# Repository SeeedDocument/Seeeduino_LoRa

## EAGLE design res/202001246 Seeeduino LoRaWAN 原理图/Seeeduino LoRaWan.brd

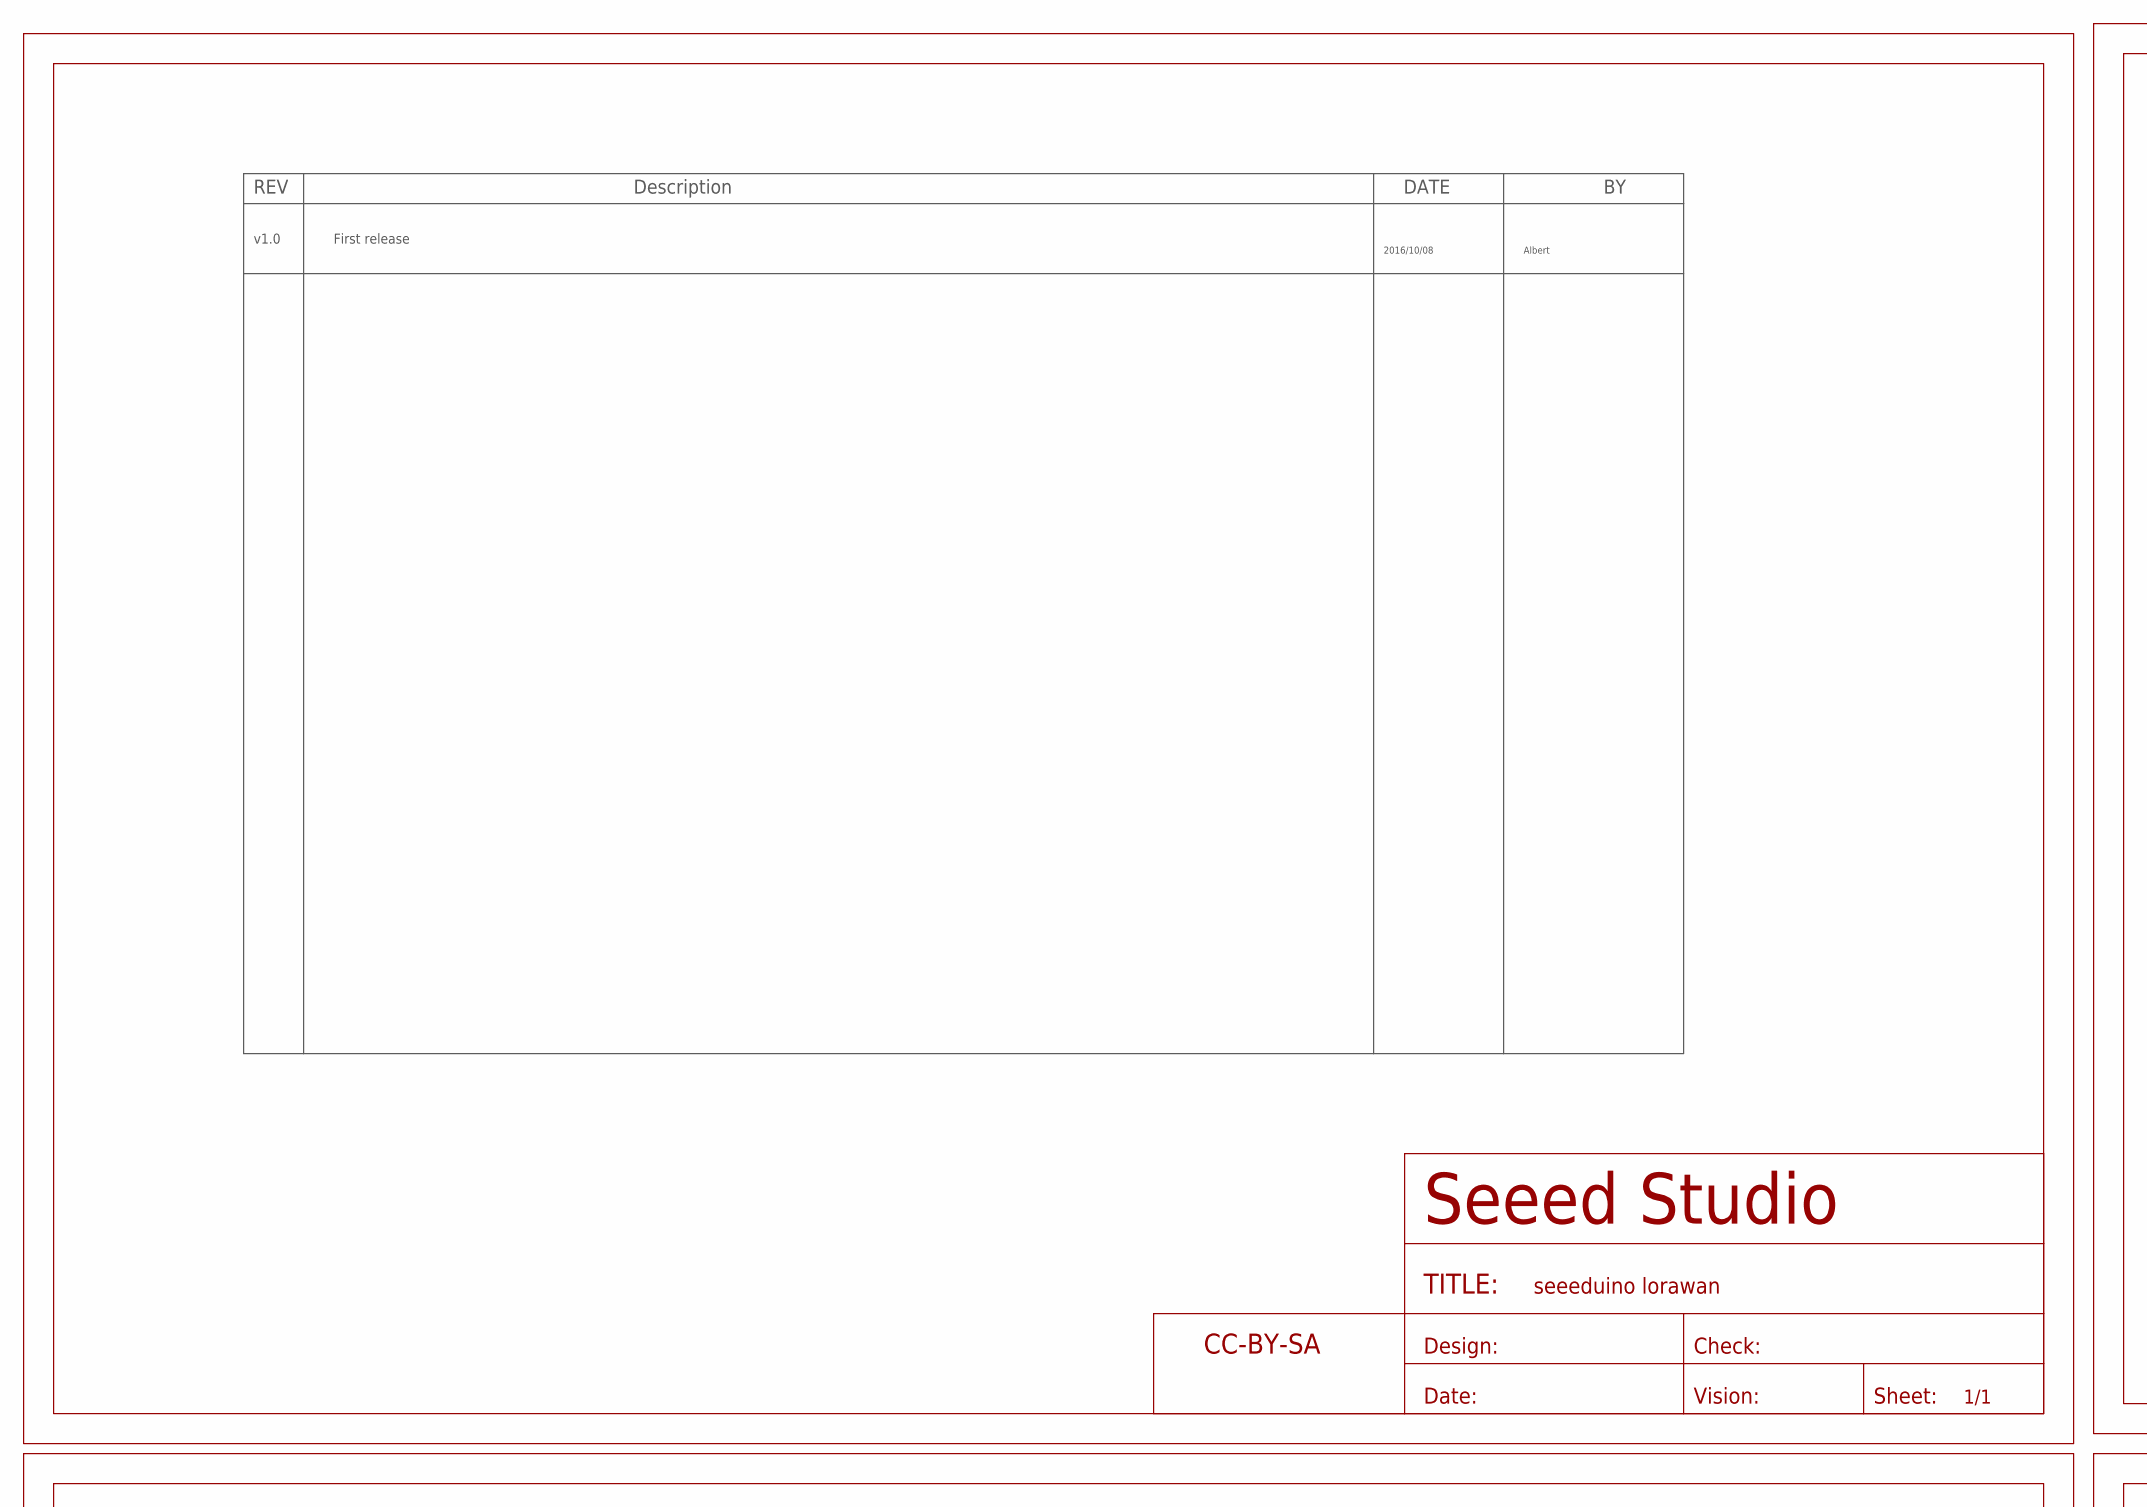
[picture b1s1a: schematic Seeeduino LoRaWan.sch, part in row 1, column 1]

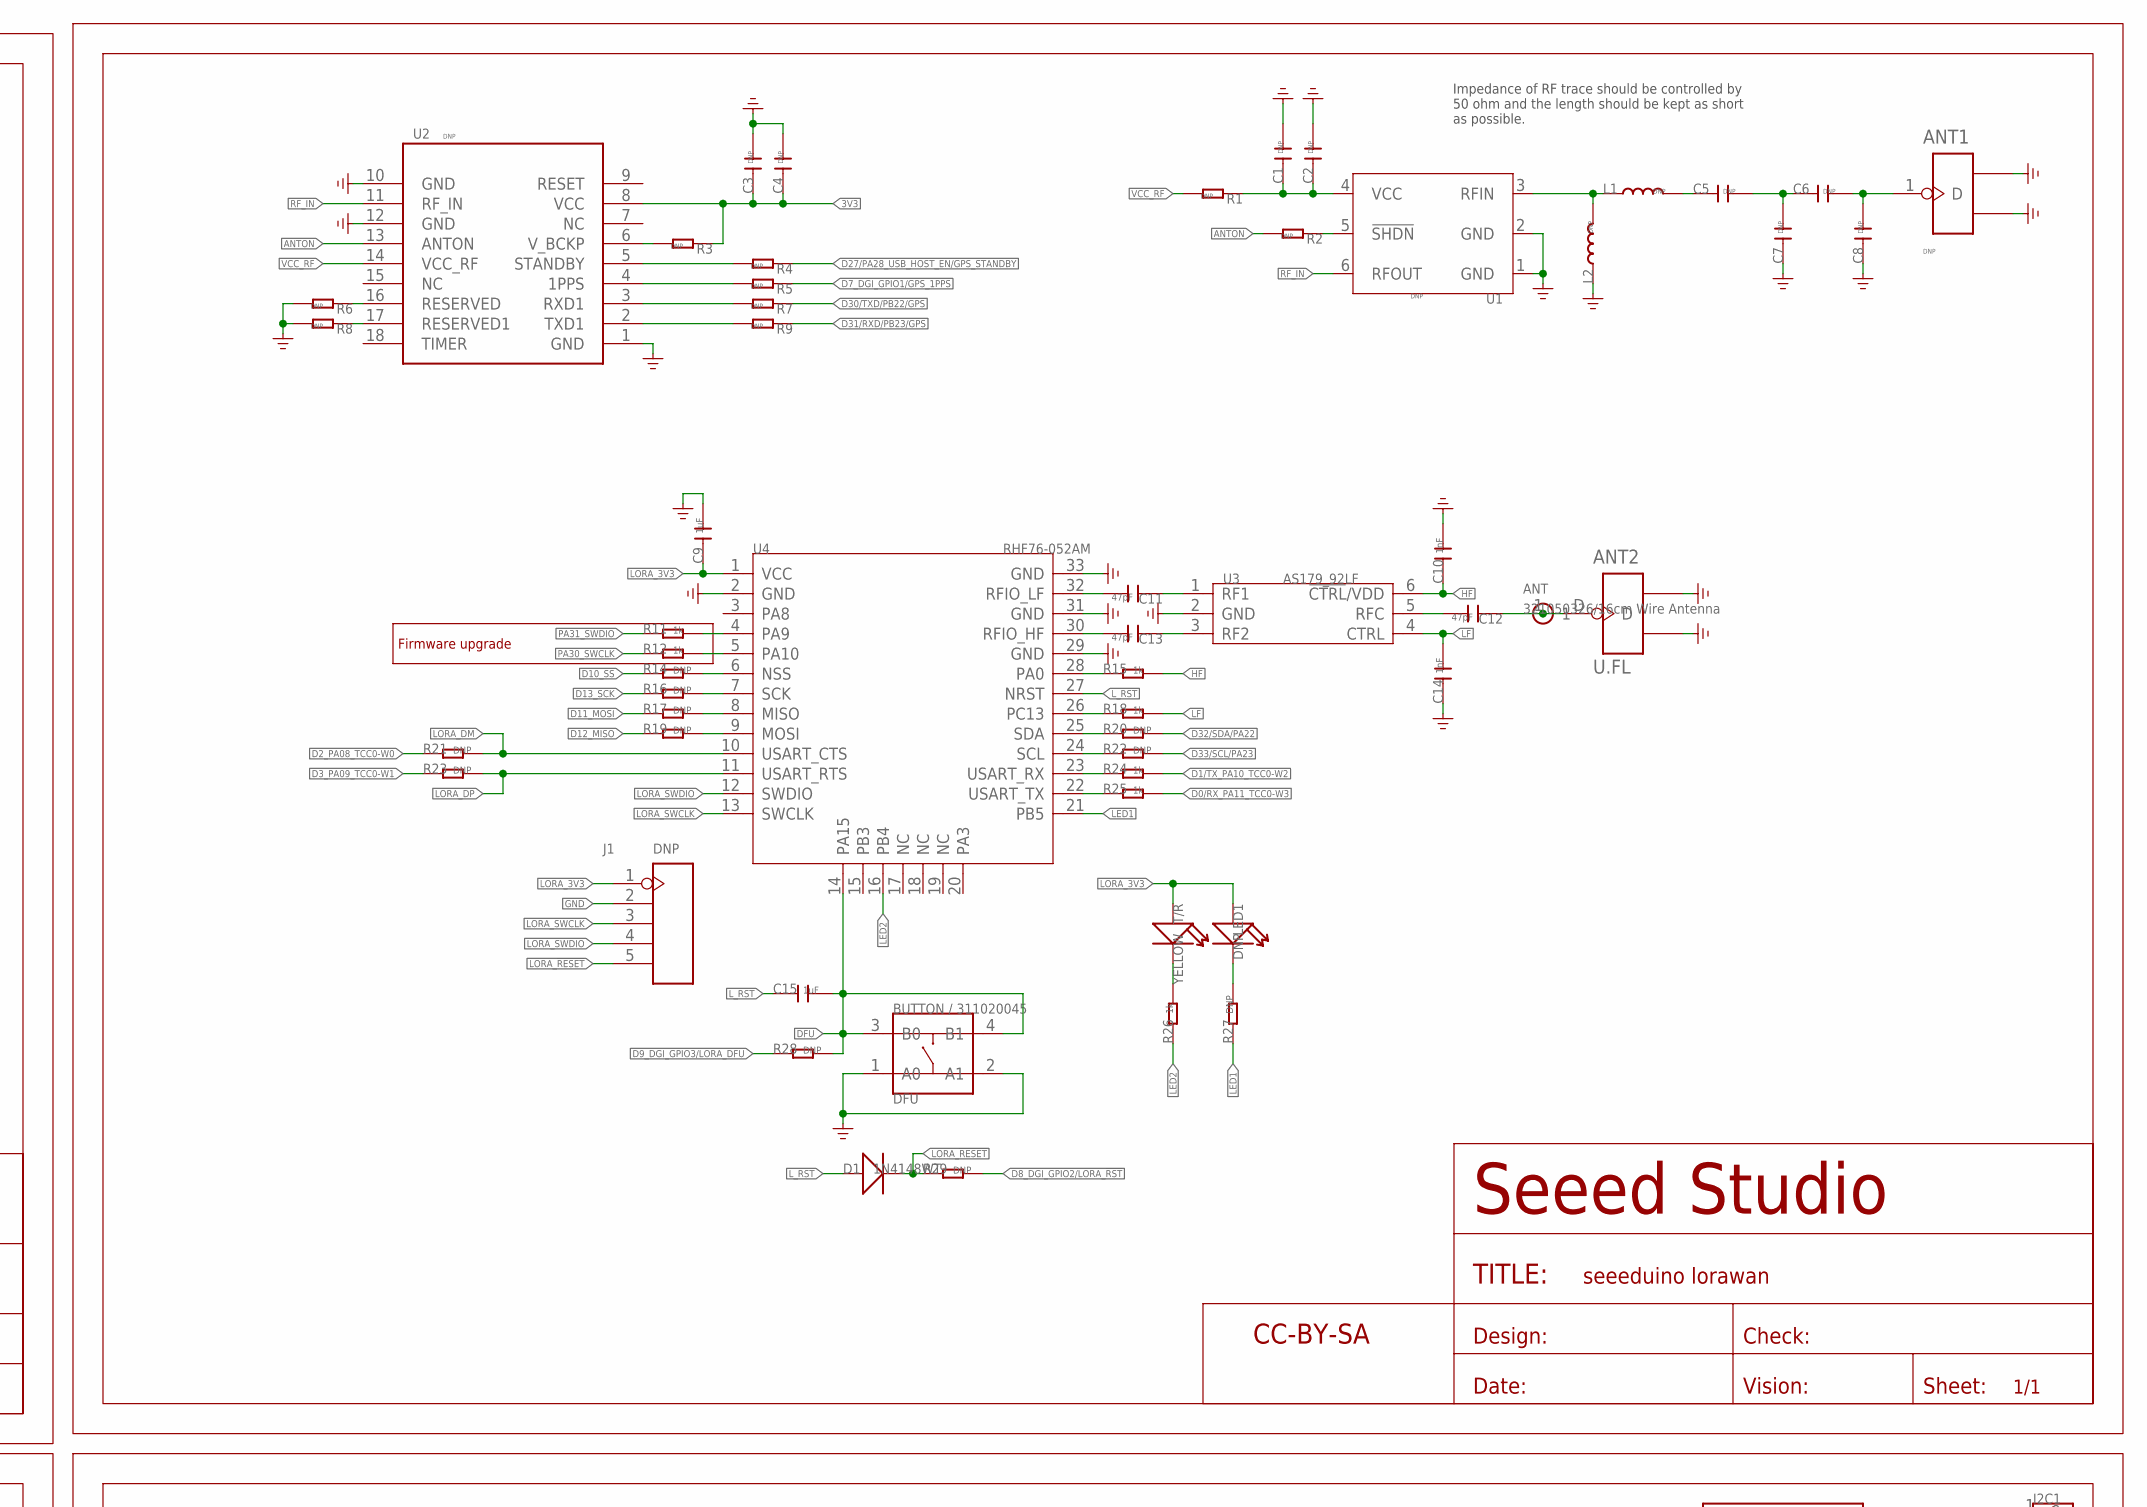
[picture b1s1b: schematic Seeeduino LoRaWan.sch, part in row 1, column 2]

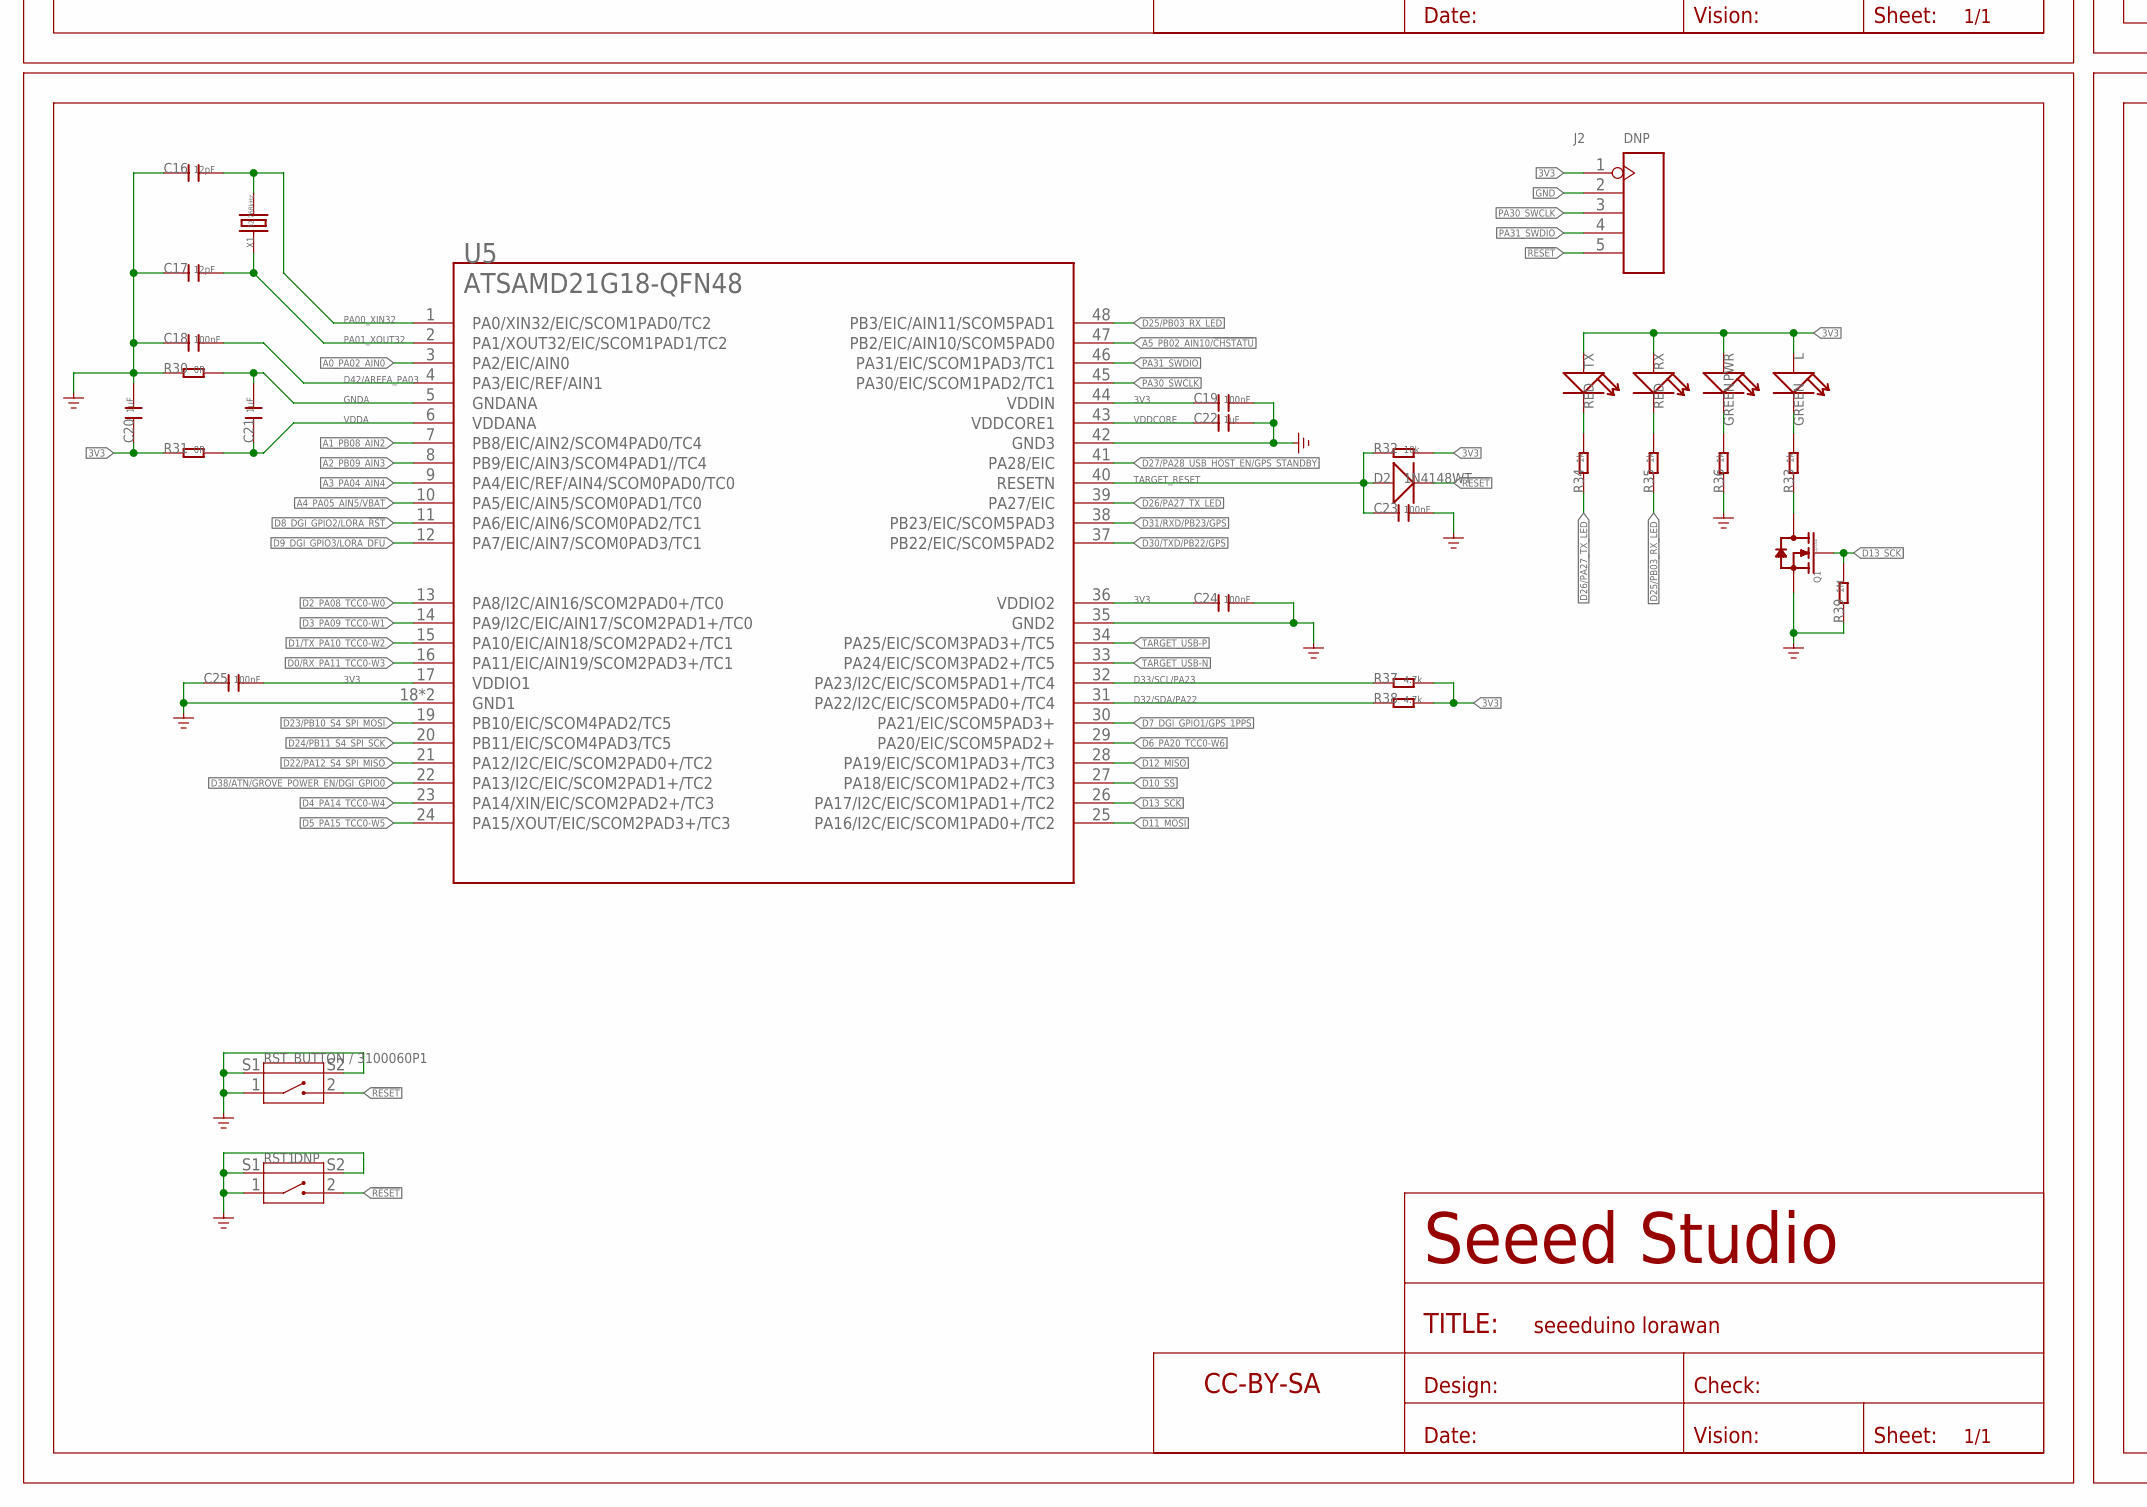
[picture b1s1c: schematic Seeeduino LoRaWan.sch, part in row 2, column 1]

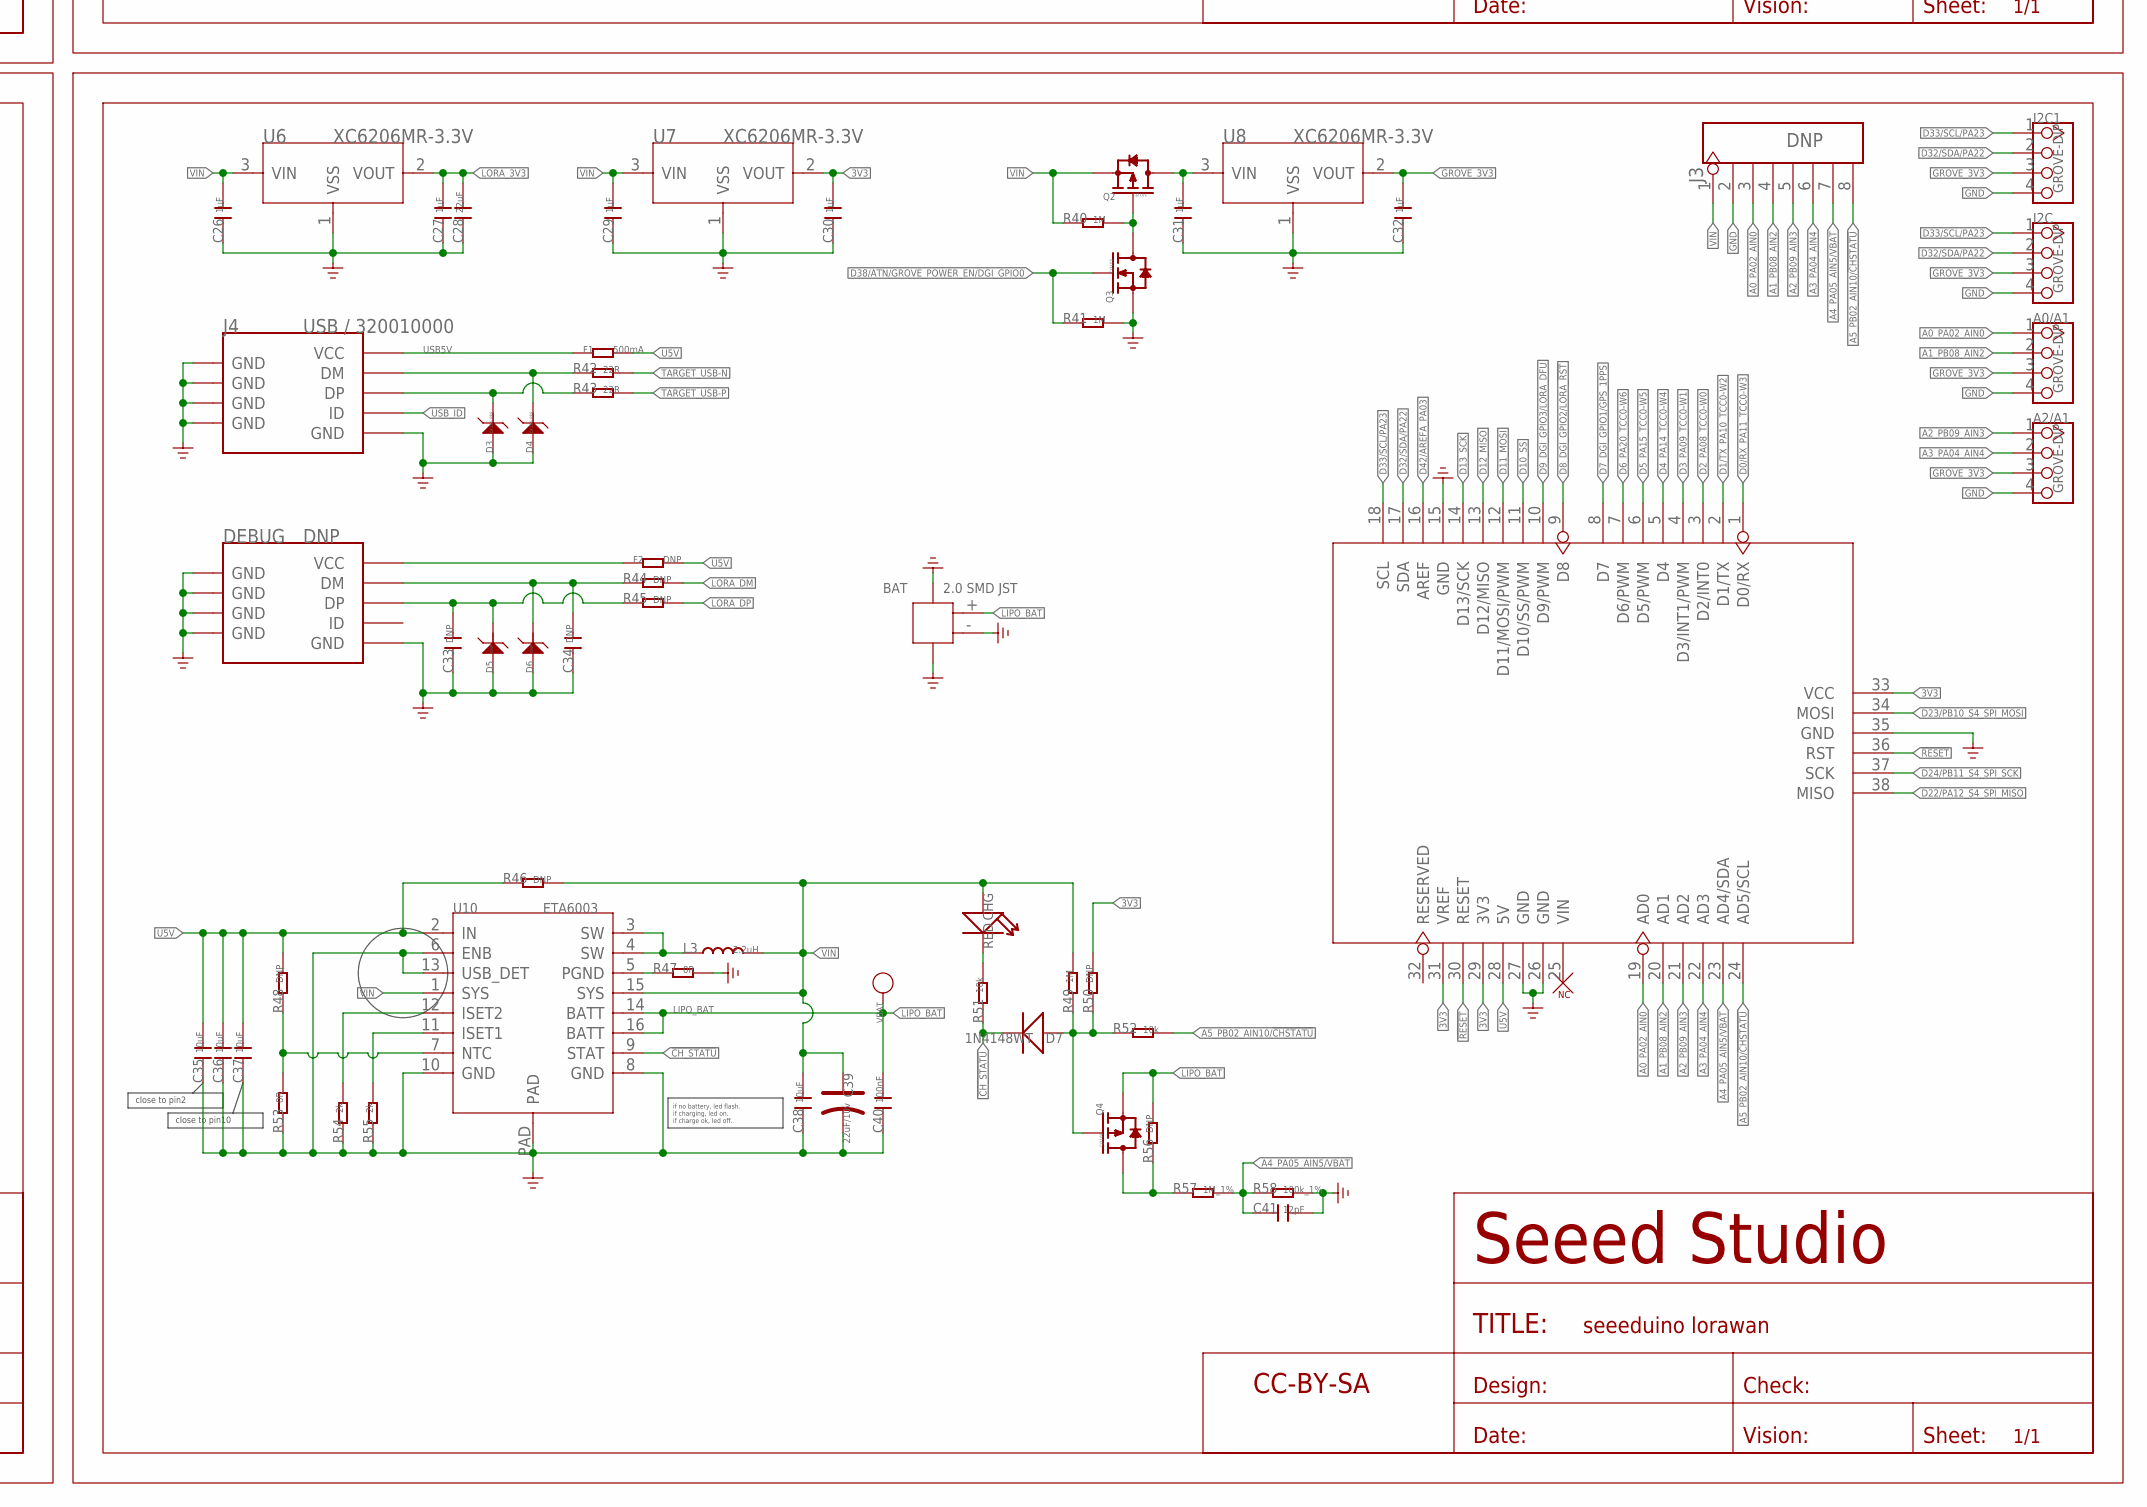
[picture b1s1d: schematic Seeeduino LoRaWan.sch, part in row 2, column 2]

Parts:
A0/A1, A2/A1: GROVE-DIP; 4P-2.0
ANT: 321050326/16cm Wire Antenna; 1P-65/35MIL
ANT1: DNP; ANT3-SMD-5.2X3.7X0.7MM
ANT2: U.FL; U-FL3P-SMD-2.6X2.6X1.0MM
BAT: 2.0 SMD JST; HW2-SMD-2.0-90D
C1, C2, C3, C5, C6, C7, C8, C33, C34: DNP; C0402
C4: DNP; C0603
C9, C15, C20, C21, C22, C26, C27, C29, C30, C31, C32: 1uF; C0402
C10, C14: 1nF; C0402
C11, C12, C13: 47pF; C0402
C16, C17, C41: 12pF; C0402
C18, C19, C23, C24, C25, C40: 100nF; C0402
C28: 22uF; C0603
C35, C36, C37, C38: 10uF; C0603
C39: 22uF/10v; AVX-A
CHG: RED; LED-0603
D1, D2, D7: 1N4148WT; SOD523
D3, D4: DF2S6.8FS; SOD-923
D5, D6: DNP; SOD-923
DEBUG: DNP; MICRO-USB
DFU: BUTTON / 311020045; SW4P-SMD-4.5X3.2X2.5MM
F1: 500mA; R0805
F2: DNP; R0805
FR, FR1: PAGE1; SEEEDSTUDIO-PCB-FRAME
I2C, I2C1: GROVE-DIP; 4P-2.0
J1, J2: DNP; H5-SMD-2.0-TEST
J3: DNP; 8P-2.54-65/35MIL
J4: USB / 320010000; MICRO-USB
L: GREEN; LED-0603
L1, L2: DNP; L0402
L3: 2.2uH; L0805
LED1: DNP; LED-0603
PWR: GREEN; LED-0603
Q1, Q3: CJ2102; SOT-323
Q2, Q4: CJ2101; SOT323
R1, R2, R3, R4, R5, R6, R7, R8, R9, R14, R16, R17, R19, R20, R21, R22, R23, R27, R28, R29, R44, R45, R46, R48, R50, R56: DNP; R0402
R11, R12, R15, R18, R24, R25, R26, R33, R34, R35, R36: 1k; R0402
R30, R31, R47, R53: 0R; R0402
R32, R51, R52: 10k; R0402
R37, R38: 4.7k; R0402
R39, R40, R41, R49: 1M; R0402
R42, R43: 22R; R0402
R54, R55: 2k; R0402
R57: 1M_1%; R0402
R58: 100k_1%; R0402
RST: BUTTON / 3100060P1; 4P-SMD-7.0X3.5X3.5H-90D
RST1: DNP; 4P-SMD-7.0X3.5X3.5H-90D
RX: RED; LED-0603
T/R: YELLOW; LED-0603
TX: RED; LED-0603
U1: DNP; DFN6-0.5-1.5X1.2X0.72MM
U2: DNP; LGA18-1.1-9.7X10.1X2.5MM
U3: AS179_92LF; SC-70
U4: RHF76-052AM; MODULE33P-SMD-2.0-28X23X2.9MM
U5: ATSAMD21G18-QFN48; QFN48-7X7
U6, U7, U8: XC6206MR-3.3V; SOT23
U9: ARDUINO-38P
U10: ETA6003; QFN16G-0.5-3X3MM
U$2, U$3: SEEEDSTUDIO-OPEN-SCH-FRAME; SEEEDSTUDIO-PCB-FRAME
VBAT: DNP; TP_4545
X1: 32.768kHz; X2-SMD-3.2X1.5X0.55MM

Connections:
3V3: C3.1, C4.1, C19.1, C20.1, C24.1, C25.2, C30.2, J2.1, L.+, PWR.+, R3.1, R31.1, R32.2, R37.2, R38.2, R50.2, RX.+, TX.+, U2.8 (VCC), U5.17 (VDDIO1), U5.36 (VDDIO2), U5.44 (VDDIN), U7.2 (VOUT), U9.29 (3V3), U9.31 (VREF), U9.33 (VCC)
!CH_STATU: D7.-, R51.1, U10.9 (STAT)
!RESET: D2.-, J2.5, RST.2, RST1.2, U9.30 (RESET), U9.36 (RST)
A0_PA02_AIN0: A0/A1.1, J3.3, U5.3 (PA2/EIC/AIN0), U9.19 (AD0)
A1_PB08_AIN2: A0/A1.2, J3.4, U5.7 (PB8/EIC/AIN2/SCOM4PAD0/TC4), U9.20 (AD1)
A2_PB09_AIN3: A2/A1.1, J3.5, U5.8 (PB9/EIC/AIN3/SCOM4PAD1//TC4), U9.21 (AD2)
A3_PA04_AIN4: A2/A1.2, J3.6, U5.9 (PA4/EIC/REF/AIN4/SCOM0PAD0/TC0), U9.22 (AD3)
A4_PA05_AIN5/VBAT: C41.1, J3.7, R57.2, R58.1, U5.10 (PA5/EIC/AIN5/SCOM0PAD1/TC0), U9.23 (AD4/SDA)
A5_PB02_AIN10/!CHSTATU: J3.8, R52.2, U5.47 (PB2/EIC/AIN10/SCOM5PAD0), U9.24 (AD5/SCL)
ANTON: R2.2, U2.13 (ANTON)
D0/RX_PA11_TCC0-W3: R25.2, U5.16 (PA11/EIC/AIN19/SCOM2PAD3+/TC1), U9.1 (D0/RX)
D1/TX_PA10_TCC0-W2: R24.2, U5.15 (PA10/EIC/AIN18/SCOM2PAD2+/TC1), U9.2 (D1/TX)
D2_PA08_TCC0-W0: R21.1, U5.13 (PA8/I2C/AIN16/SCOM2PAD0+/TC0), U9.3 (D2/INT0)
D3_PA09_TCC0-W1: R23.1, U5.14 (PA9/I2C/EIC/AIN17/SCOM2PAD1+/TC0), U9.4 (D3/INT1/PWM)
D4_PA14_TCC0-W4: U5.23 (PA14/XIN/EIC/SCOM2PAD2+/TC3), U9.5 (D4)
D5_PA15_TCC0-W5: U5.24 (PA15/XOUT/EIC/SCOM2PAD3+/TC3), U9.6 (D5/PWM)
D6_PA20_TCC0-W6: U5.29 (PA20/EIC/SCOM5PAD2+), U9.7 (D6/PWM)
D7_DGI_GPIO1/GPS_1PPS: R5.1, U5.30 (PA21/EIC/SCOM5PAD3+), U9.8 (D7)
D8_DGI_GPIO2/LORA_!RST: R29.2, U5.11 (PA6/EIC/AIN6/SCOM0PAD2/TC1), U9.9 (D8)
D9_DGI_GPIO3/LORA_DFU: R28.1, U5.12 (PA7/EIC/AIN7/SCOM0PAD3/TC1), U9.10 (D9/PWM)
D10_SS: R14.1, U5.27 (PA18/EIC/SCOM1PAD2+/TC3), U9.11 (D10/SS/PWM)
D11_MOSI: R17.1, U5.25 (PA16/I2C/EIC/SCOM1PAD0+/TC2), U9.12 (D11/MOSI/PWM)
D12_MISO: R19.1, U5.28 (PA19/EIC/SCOM1PAD3+/TC3), U9.13 (D12/MISO)
D13_SCK: Q1.1 (G), R16.1, R39.2, U5.26 (PA17/I2C/EIC/SCOM1PAD1+/TC2), U9.14 (D13/SCK)
D22/PA12_S4_SPI_MISO: U5.21 (PA12/I2C/EIC/SCOM2PAD0+/TC2), U9.38 (MISO)
D23/PB10_S4_SPI_MOSI: U5.19 (PB10/EIC/SCOM4PAD2/TC5), U9.34 (MOSI)
D24/PB11_S4_SPI_SCK: U5.20 (PB11/EIC/SCOM4PAD3/TC5), U9.37 (SCK)
D25/PB03_RX_LED: R35.1, U5.48 (PB3/EIC/AIN11/SCOM5PAD1)
D26/PA27_TX_LED: R34.1, U5.39 (PA27/EIC)
D27/PA28_USB_HOST_EN/GPS_STANDBY: R4.1, U5.41 (PA28/EIC)
D30/TXD/PB22/GPS: R7.1, U5.37 (PB22/EIC/SCOM5PAD2)
D31/RXD/PB23/GPS: R9.1, U5.38 (PB23/EIC/SCOM5PAD3)
D32/SDA/PA22: I2C.2, I2C1.2, R20.2, R38.1, U5.31 (PA22/I2C/EIC/SCOM5PAD0+/TC4), U9.17 (SDA)
D33/SCL/PA23: I2C.1, I2C1.1, R22.2, R37.1, U5.32 (PA23/I2C/EIC/SCOM5PAD1+/TC4), U9.18 (SCL)
D38/ATN/GROVE_POWER_EN/DGI_GPIO0: Q3.1 (G), R41.1, U5.22 (PA13/I2C/EIC/SCOM2PAD1+/TC2)
D42/AREFA_PA03: C18.2, U5.4 (PA3/EIC/REF/AIN1), U9.16 (AREF)
DFU: C15.2, DFU.3 (B0), DFU.4 (B1), R28.2, U4.14 (PA15)
GND: A0/A1.4, A2/A1.4, ANT1.2 (GND1), ANT1.3 (GND2), ANT2.GND1, ANT2.GND2, BAT.3, BAT.4, BAT.- (2), C1.2, C2.2, C3.2, C4.2, C7.1, C8.1, C9.2, C10.2, C14.1, C16.1, C17.1, C18.1, C19.2, C20.2, C22.2, C23.2, C24.2, C25.1, C26.1, C27.1, C28.1, C29.1, C30.1, C31.1, C32.1, C33.1, C34.1, C35.1, C36.1, C37.1, C38.1, C39.-, C40.1, C41.2, D3.2 (1), D4.2 (1), D5.2 (1), D6.2 (1), DEBUG.5 (GND), DEBUG.S1 (GND), DEBUG.S2 (GND), DEBUG.S3 (GND), DEBUG.S4 (GND), DEBUG.S5 (GND), DEBUG.S6 (GND), DFU.1 (A0), DFU.2 (A1), I2C.4, I2C1.4, J1.2, J2.2, J3.2, J4.5 (GND), J4.S1 (GND), J4.S2 (GND), J4.S3 (GND), J4.S4 (GND), J4.S5 (GND), J4.S6 (GND), L2.1, Q1.2 (S), Q3.2 (S), R6.2, R8.2, R30.1, R36.1, R39.1, R41.2, R47.2, R53.1, R54.1, R55.1, R58.2, RST.1, RST.S1, RST.S2, RST1.1, RST1.S1, RST1.S2, U1.1 (GND), U1.2 (GND), U2.1 (GND), U2.10 (GND), U2.12 (GND), U3.2 (GND), U4.2 (GND), U4.29 (GND), U4.31 (GND), U4.33 (GND), U5.18 (GND1), U5.35 (GND2), U5.42 (GND3), U5.PAD (GND1), U6.1 (VSS), U7.1 (VSS), U8.1 (VSS), U9.15 (GND), U9.26 (GND), U9.27 (GND), U9.35 (GND), U10.6 (ENB), U10.8 (GND), U10.10 (GND), U10.13 (USB_DET), U10.PAD
GNDA: C21.2, R30.2, U5.5 (GNDANA)
GROVE_3V3: A0/A1.3, A2/A1.3, C32.2, I2C.3, I2C1.3, U8.2 (VOUT)
HF: C10.1, R15.2, U3.6 (!CTRL!/VDD)
LED1: R27.1, U4.21 (PB5)
LED2: R26.1, U4.16 (PB4)
LF: C14.2, R18.2, U3.4 (CTRL)
LIPO_BAT: BAT.+ (1), C40.2, Q4.2 (S), R56.2, U10.14 (BATT), U10.16 (BATT), VBAT.T
LORA_3V3: C9.1, C27.2, C28.2, J1.1, LED1.+, T/R.+, U4.1 (VCC), U6.2 (VOUT)
LORA_!RESET: D1.-, J1.5, R29.1
LORA_DM: R21.2, R44.2, U4.10 (USART_CTS)
LORA_DP: R23.2, R45.2, U4.11 (USART_RTS)
LORA_SWCLK: J1.3, U4.13 (SWCLK)
LORA_SWDIO: J1.4, U4.12 (SWDIO)
L_RST: C15.1, D1.+, U4.27 (NRST)
unnamed: Q1.3 (D), R33.1
unnamed: R34.2, TX.-
unnamed: C5.2, C6.1, C7.2
unnamed: R35.2, RX.-
unnamed: L.-, R33.2
unnamed: ANT1.1 (D), C6.2, C8.2
unnamed: D3.1 (2), J4.3 (DP), R43.1
unnamed: L1.1, L2.2, U1.3 (RFIN)
unnamed: C33.2, D5.1 (2), DEBUG.3 (DP), R45.1
unnamed: D4.1 (2), J4.2 (DM), R42.1
unnamed: C5.1, L1.2
unnamed: PWR.-, R36.2
unnamed: R2.1, U1.5 (!SHDN)
unnamed: C1.1, C2.1, R1.1, U1.4 (VCC)
unnamed: DEBUG.1 (VCC), F2.1
unnamed: R6.1, U2.16 (RESERVED)
unnamed: R8.1, U2.17 (RESERVED1)
unnamed: R3.2, U2.6 (V_BCKP)
unnamed: R4.2, U2.5 (STANDBY)
unnamed: R5.2, U2.4 (1PPS)
unnamed: R48.1, R53.2, U10.7 (NTC)
unnamed: R55.2, U10.11 (ISET1)
unnamed: C34.2, D6.1 (2), DEBUG.2 (DM), R44.1
unnamed: C12.2, U3.5 (RFC)
unnamed: C11.2, U4.32 (RFIO_LF)
unnamed: C13.2, U4.30 (RFIO_HF)
unnamed: R54.2, U10.12 (ISET2)
unnamed: R24.1, U4.23 (USART_RX)
unnamed: R47.1, U10.5 (PGND)
unnamed: R25.1, U4.22 (USART_TX)
unnamed: R11.2, U4.4 (PA9)
unnamed: R12.2, U4.5 (PA10)
unnamed: CHG.-, R51.2
unnamed: Q4.3 (D), R56.1, R57.1
unnamed: R20.1, U4.25 (SDA)
unnamed: R22.1, U4.24 (SCL)
unnamed: R19.2, U4.9 (MOSI)
unnamed: R17.2, U4.8 (MISO)
unnamed: R16.2, U4.7 (SCK)
unnamed: R14.2, U4.6 (NSS)
unnamed: C31.2, Q2.3 (D), U8.3 (VIN)
unnamed: R26.2, T/R.-
unnamed: LED1.-, R27.2
unnamed: R15.1, U4.28 (PA0)
unnamed: R18.1, U4.26 (PC13)
unnamed: Q2.1 (G), Q3.3 (D), R40.2
unnamed: D7.+, Q4.1 (G), R49.1, R50.1, R52.1
unnamed: C11.1, U3.1 (RF1)
unnamed: C13.1, U3.3 (RF2)
unnamed: ANT.1, ANT2.D, C12.1
unnamed: L3.1, U10.3 (SW), U10.4 (SW)
PA00_XIN32: C16.2, U5.1 (PA0/XIN32/EIC/SCOM1PAD0/TC2), X1.2
PA01_XOUT32: C17.2, U5.2 (PA1/XOUT32/EIC/SCOM1PAD1/TC2), X1.1
PA30_SWCLK: J2.3, R12.1, U5.45 (PA30/EIC/SCOM1PAD2/TC1)
PA31_SWDIO: J2.4, R11.1, U5.46 (PA31/EIC/SCOM1PAD3/TC1)
RF_IN: U1.6 (RFOUT), U2.11 (RF_IN)
RXD1: R7.2, U2.3 (RXD1)
TARGET_RESET: C23.1, D2.+, R32.1, U5.40 (RESETN)
TARGET_USB-N: R42.2, U5.33 (PA24/EIC/SCOM3PAD2+/TC5)
TARGET_USB-P: R43.2, U5.34 (PA25/EIC/SCOM3PAD3+/TC5)
TXD1: R9.2, U2.2 (TXD1)
U5V: C35.2, C36.2, C37.2, F1.2, F2.2, R46.1, R48.2, U9.28 (5V), U10.2 (IN)
USB5V: F1.1, J4.1 (VCC)
USB_ID: J4.4 (ID)
VCC_RF: R1.2, U2.14 (VCC_RF)
VDDA: C21.1, R31.2, U5.6 (VDDANA)
VDDCORE: C22.1, U5.43 (VDDCORE1)
VIN: C26.2, C29.2, C38.2, C39.+, CHG.+, J3.1, L3.2, Q2.2 (S), R40.1, R46.2, R49.2, U6.3 (VIN), U7.3 (VIN), U10.1 (SYS), U10.15 (SYS)

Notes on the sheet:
Impedance of RF trace should be controlled by 50 ohm and the length should be kept as short as possible.
close to pin10
if no battery, led flash. if charging, led on. if charge ok, led off.
close to pin2
Firmware upgrade
v1.0
First release
2016/10/08
Albert

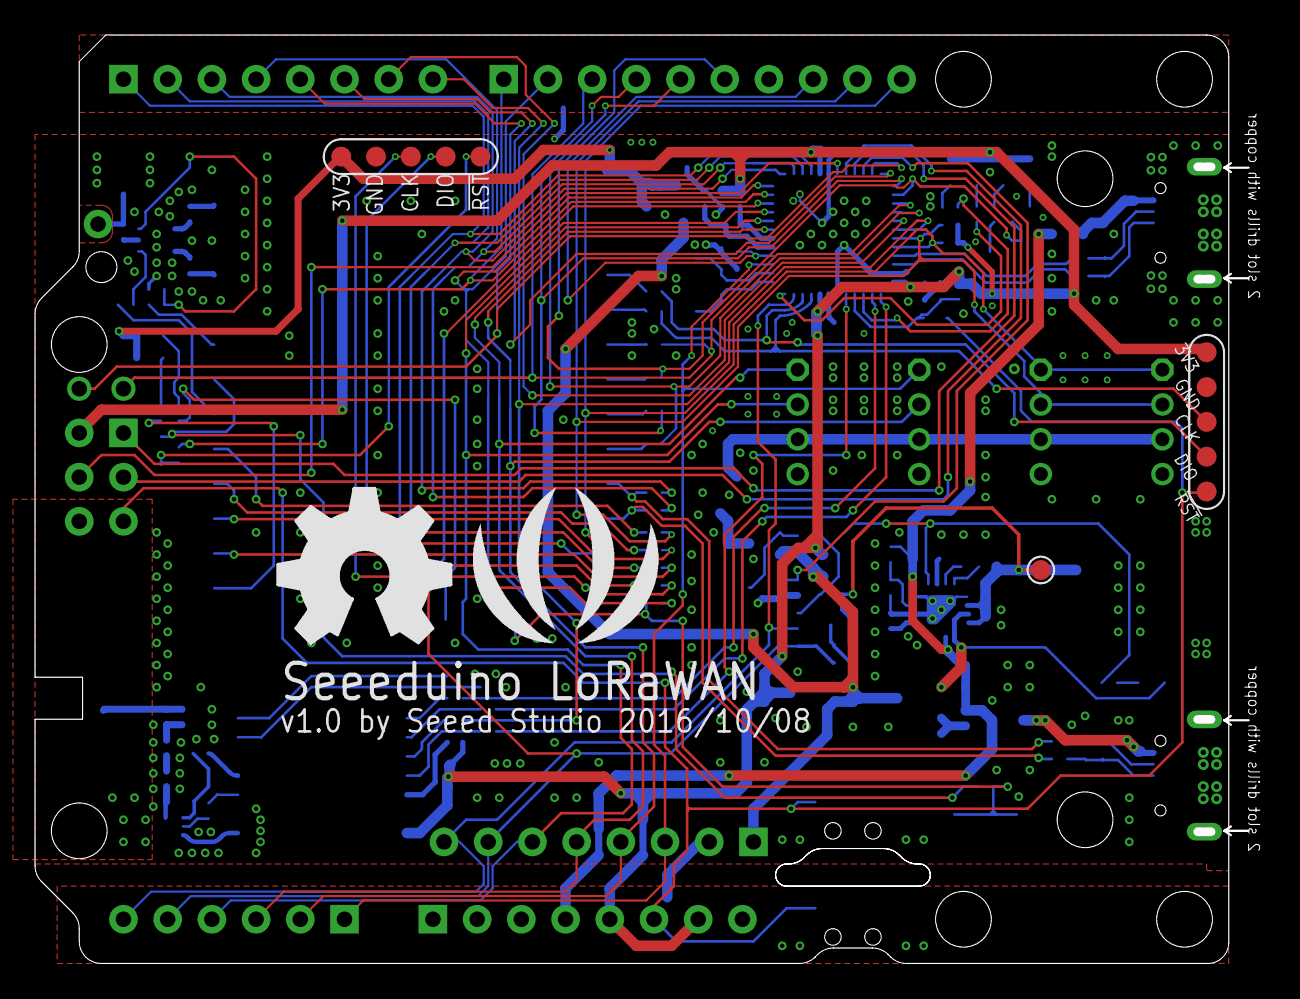
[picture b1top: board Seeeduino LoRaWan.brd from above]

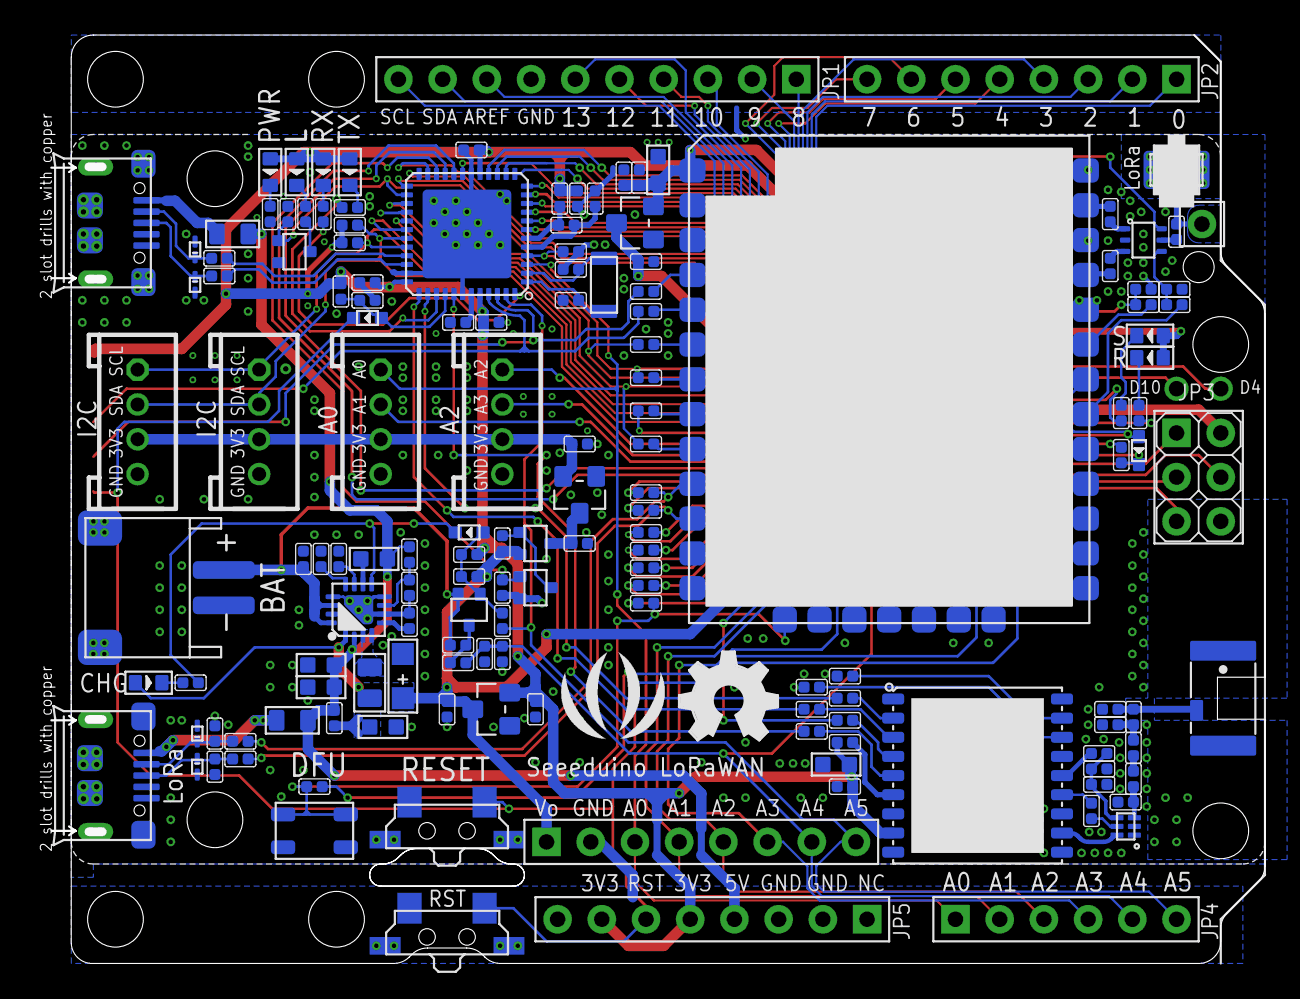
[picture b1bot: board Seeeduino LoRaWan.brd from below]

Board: 2 copper layers, 69.7 x 53.3 mm, 156 parts (151 on the bottom side), 119 nets.

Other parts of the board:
U$1: OSHW_FILLX350_NOTEXT
U$17: OSHW_FILLX200_NOTEXT_TNAME
U$25: SEEED-SILK-280*268MIL
U$27: SEEED-SILK-420X352

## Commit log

2016-10-31 add image arudino
2016-10-31 test
2016-11-01 add board_lora.png
2016-11-01 add river
2016-11-01 add device manager
2016-11-01 update device_manager
2016-11-01 add images
2016-11-01 update images
2016-11-01 image
2016-11-01 add pin map
2016-11-01 update driver
2016-11-02 add cover
2016-11-03 update firmware images
2016-11-03 download firmware image
2016-11-03 add resources
2016-12-20 add image
2016-12-20 add gps image
2016-12-20 change cover
2019-03-05 add v2.1.19 firmware

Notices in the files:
parts and their libraries:
moudle-new: This work is licensed under the Creative Commons Attribution 4.0 International License.
To view a copy of this license,visit:
http://creativecommons.org/licenses/by-sa/4.0
moudle-new: CC-BY-SA
